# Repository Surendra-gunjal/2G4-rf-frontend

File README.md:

# 2.4 GHz RF Receiver Front-End (MAX2644 LNA + 2.4 GHz band-pass filter)

KiCad 8 project for a 2.4 GHz receiver front end: SMA in, Johanson 2450BP14D0100001T band-pass filter, MAX2644 LNA with the datasheet input match, 3.3 V supply, SMA out. Board stack-up: Rogers RO4003C 0.813 mm, 35 um copper, grounded coplanar waveguide RF lines (W 1.6 mm, gap 0.3 mm).

**Status: layout draft. Not fabrication-validated.** Run DRC and ERC in KiCad and read `docs/LAYOUT_NOTES.md` (open items and a pre-fabrication checklist) before ordering boards.

## Layout
- `hardware/` KiCad project (`.kicad_pcb`, `.kicad_sch`, `.kicad_pro`) and the generic footprint library
- `scripts/` Python that generates the PCB and schematic from parameters, a 50 ohm line solver, and geometry/netlist checks
- `docs/` layout notes, previews, and the project plan (`RF_Frontend_Project_Plan.xlsx`)
- `reference/` the original README and BOM the design started from

## Regenerating
```
cd scripts
python3 gen_pcb.py   # needs: shapely
python3 gen_sch.py
```
Paths inside the scripts point at the original working folder; edit the output paths at the top of each script first.

## Known limitations
- Footprints for the SMA connectors, filter and SC70-6 are generic placeholders; use the vendor footprints.
- The input-match topology (L1 position) and the C3 / L2 variant must be confirmed against the MAX2644 datasheet.
- The 50 ohm width comes from a quasi-static solver (about +/-2.5%), not an EM simulation or measurement.

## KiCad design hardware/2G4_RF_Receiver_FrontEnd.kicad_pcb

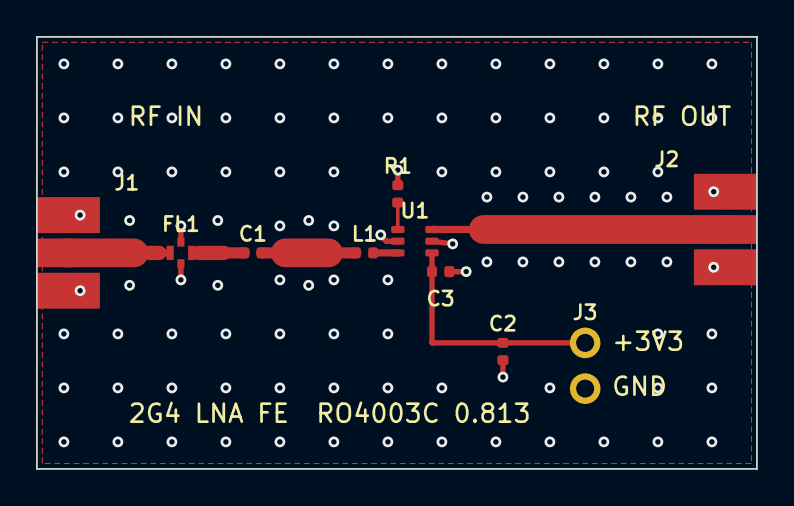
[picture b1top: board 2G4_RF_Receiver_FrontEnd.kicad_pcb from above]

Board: 2 copper layers, 40.0 x 24.0 mm, 10 parts (0 on the bottom side), 8 nets.

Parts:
C1: 33pF C0G; C_R_L_0402_P1L
C2: 33pF C0G; C_R_L_0402_P1T
C3: 15pF C0G; C_R_L_0402_P1L
FL1: Johanson 2450BP14D0100001T; BPF_0603_Johanson_RECONSTRUCTED
J1: SMA edge-launch 50R (PLACEHOLDER); SMA_EdgeLaunch_PLACEHOLDER_W
J2: SMA edge-launch 50R (PLACEHOLDER); SMA_EdgeLaunch_PLACEHOLDER_E
J3: 3V3 / GND; PinHeader_1x02_P2.54mm
L1: 3.3nH RF; C_R_L_0402_P1L
R1: 1.2k 1%; C_R_L_0402_P1B
U1: MAX2644EXT+; SC70-6_MAX2644

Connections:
+3V3: C2.1, C3.1, J3.1 (3V3), U1.4 (VCC)
BIAS: R1.1, U1.1 (BIAS)
GND: C2.2, C3.2, FL1.1 (GND), FL1.3 (GND), J1.2 (GND), J1.3 (GND), J1.4 (GND), J2.2 (GND), J2.3 (GND), J2.4 (GND), J3.2 (GND), R1.2, U1.2 (GND), U1.5 (GND)
RF_BPF_OUT: C1.1, FL1.4 (I/O)
RF_IN: FL1.2 (I/O), J1.1 (SIGNAL)
RF_LNA_IN: L1.2, U1.3 (RFIN)
RF_MATCH_A: C1.2, L1.1
RF_OUT: J2.1 (SIGNAL), U1.6 (RFOUT)

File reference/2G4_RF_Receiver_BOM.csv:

RefDes,Qty,Part / value,Package / notes,Link
U1,1,MAX2644EXT+,SC70-6 2.4 GHz LNA; verify current stock and package marking,https://www.analog.com/en/products/max2644.html
FL1,1,Johanson 2450BP14D0100001T,"0603 BPF, 2400-2500 MHz, 1.5 dB typ / 1.7 dB max insertion loss",https://www.johansontechnology.com/products/integrated-passi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
C1,1,33 pF C0G/NP0 ±5%,0402 RF capacitor; manufacturer reference value,https://www.digikey.in/
L1,1,3.3 nH high-Q RF inductor,0402 RF inductor; use a part with self-resonance comfortably above 2.45 GHz; reference value,https://www.coilcraft.com/
R1,1,1.2 kΩ 1%,0402 resistor; MAX2644 bias programming reference circuit,https://www.digikey.in/
C2,1,33 pF C0G/NP0 ±5%,0402 bypass capacitor; place per datasheet layout,https://www.digikey.in/
C3,1,15 pF C0G/NP0 ±5%,0402 bypass capacitor; place very close to IC per datasheet layout,https://www.digikey.in/
"J1,J2",2,50 Ω SMA female edge-launch,Choose connector footprint to match final PCB thickness and vendor footprint,https://www.digikey.in/
J3,1,2-pin power connector or test pads,3.3 V input and GND,https://www.digikey.in/
PCB,1,Rogers RO4003C,Choose exact dielectric thickness and copper weight with manufacturer before line-width calculation,https://www.rogerscorp.com/advanced-electronics-solutions/ro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
